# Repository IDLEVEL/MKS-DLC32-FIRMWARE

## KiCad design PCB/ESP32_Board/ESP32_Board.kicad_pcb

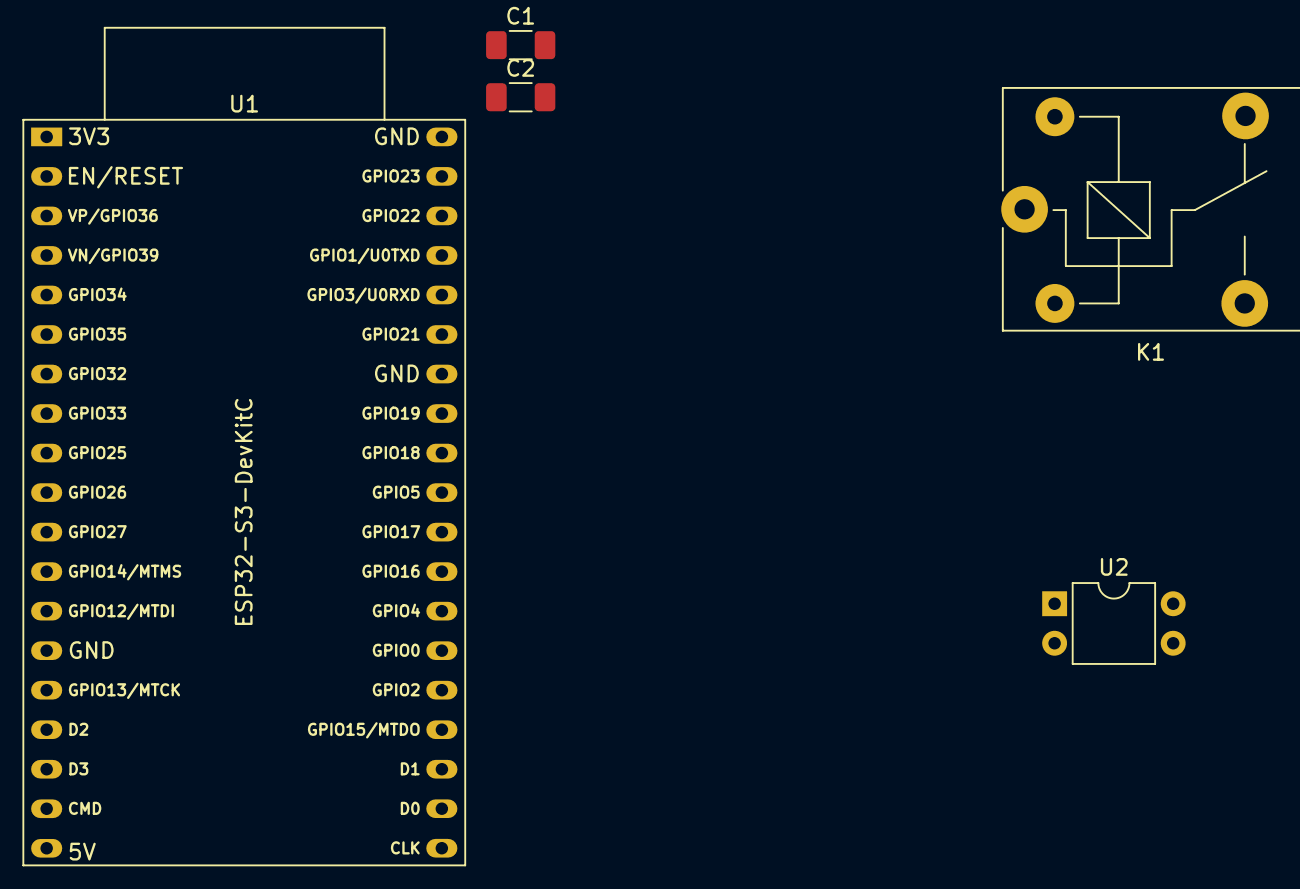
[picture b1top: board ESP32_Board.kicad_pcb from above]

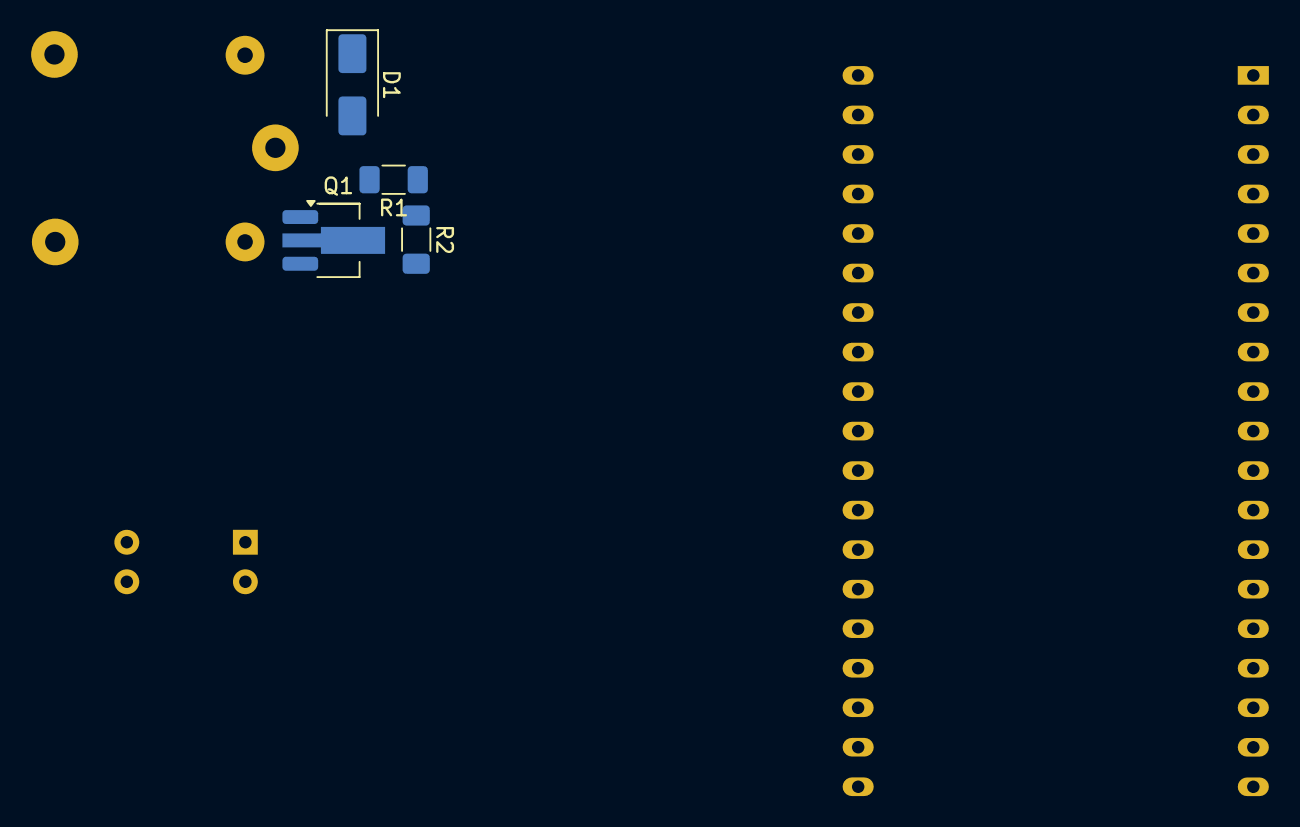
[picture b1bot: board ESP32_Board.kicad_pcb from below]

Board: 2 copper layers, 9 parts (4 on the bottom side), 6 nets, no tracks yet.

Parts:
C1, C2: C_Small; C_1206_3216Metric_Pad1.33x1.80mm_HandSolder
D1: D_Small; D_SMA
K1: SANYOU_SRD_Form_C; Relay_SPDT_SANYOU_SRD_Series_Form_C
Q1: Q_NPN_BCE; SOT-89-3_Handsoldering
R1, R2: R_Small; R_1206_3216Metric_Pad1.30x1.75mm_HandSolder
U1: ESP32-S3-DevKitC; ESP32-DevKitC
U2: PC817; DIP-4_W7.62mm

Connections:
3V3: C2.1, U1.1 (3V3)
5V: C1.1, D1.1 (K), K1.5, U1.19 (5V)
GND: C1.2, C2.2, Q1.3 (E), R2.2, U1.14 (GND), U1.32 (GND), U1.38 (GND)
unnamed: D1.2 (A), K1.2, Q1.2 (C)
unnamed: Q1.1 (B), R1.2
RELAY_LAZER: R1.1, R2.1

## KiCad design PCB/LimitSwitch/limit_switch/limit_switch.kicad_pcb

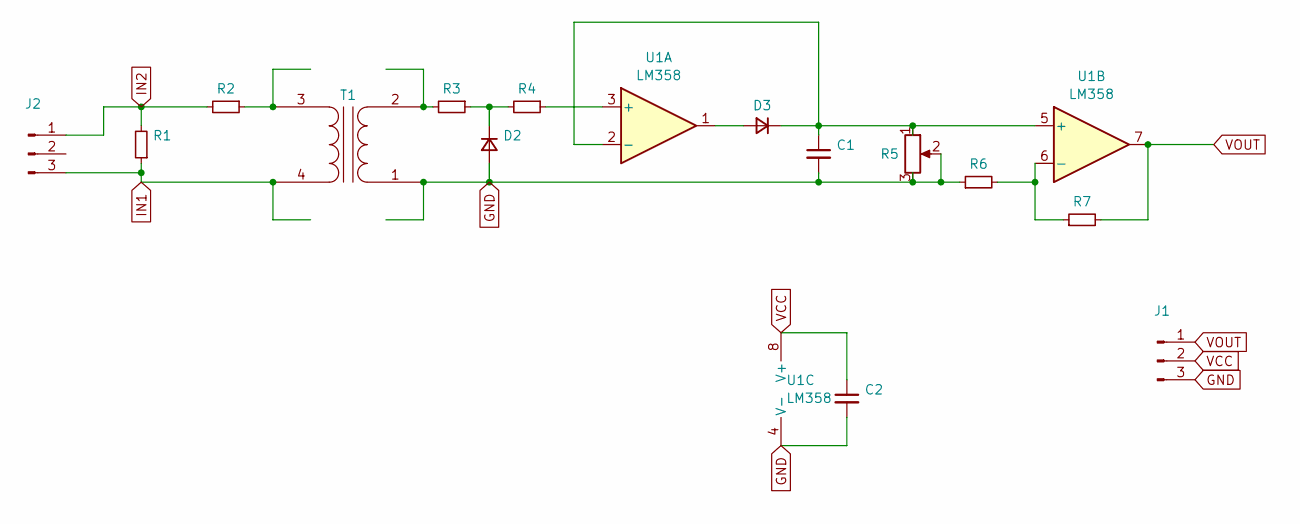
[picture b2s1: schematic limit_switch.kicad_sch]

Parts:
C1, C2: C_Small; C_1206_3216Metric_Pad1.33x1.80mm_HandSolder
D2, D3: D_Small; D_MicroMELF_Handsoldering
J1, J2: Conn_01x03_Pin; PinHeader_1x03_P2.54mm_Vertical
R1: R_Small; R_2512_6332Metric_Pad1.40x3.35mm_HandSolder
R2, R3, R4, R6, R7: R_Small; R_1206_3216Metric_Pad1.30x1.75mm_HandSolder
R5: R_Small; Potentiometer_Bourns_3266Y_Vertical
T1: Transformer_1P_1S; Transformer_Zeming_ZMPT101K
U1: LM358; SO-8_3.9x4.9mm_P1.27mm

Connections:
GND: C1.2, C2.2, D2.2 (A), J1.3, R5.2, R5.3, R6.1, T1.1 (AA), U1.4 (V-)
IN1: J2.3, R1.1, T1.4 (SB)
IN2: J2.1, R1.2, R2.2
unnamed: D2.1 (K), R3.1, R4.2
unnamed: D3.2 (A), U1.1
unnamed: C1.1, D3.1 (K), R5.1, U1.2 (-), U1.5 (+)
unnamed: R3.2, T1.2 (AB)
unnamed: R2.1, T1.3 (SA)
unnamed: R4.1, U1.3 (+)
unnamed: R6.2, R7.1, U1.6 (-)
VCC: C2.1, J1.2, U1.8 (V+)
VOUT: J1.1, R7.2, U1.7

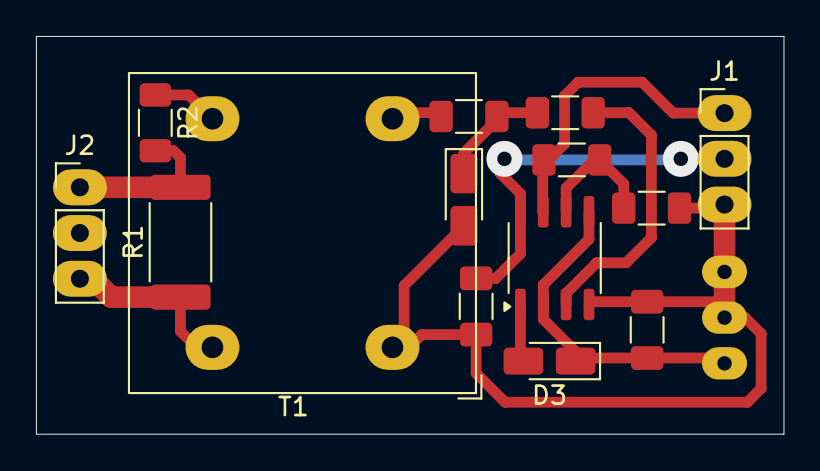
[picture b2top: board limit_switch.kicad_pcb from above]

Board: 2 copper layers, 41.5 x 22.1 mm, 15 parts (1 on the bottom side), 12 nets.

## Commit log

2024-05-12 build config
2024-08-20 .gitignore is now working
